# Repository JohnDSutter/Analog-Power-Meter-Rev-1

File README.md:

# Analog Power Meter Rev 1
 Analog RF Power Meter Designed as a CalQRP Club Project

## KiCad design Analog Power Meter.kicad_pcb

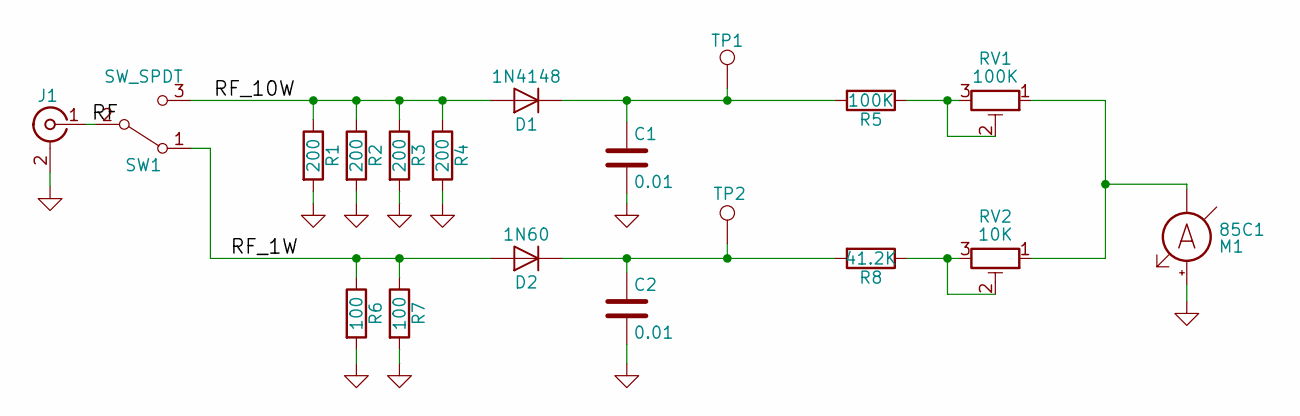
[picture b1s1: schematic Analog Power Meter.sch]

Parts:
C1, C2: 0.01; C_Disc_D3.4mm_W2.1mm_P2.50mm
D1: 1N4148; D_A-405_P7.62mm_Horizontal
D2: 1N60; D_A-405_P12.70mm_Horizontal
J1: Conn_Coaxial; BNC_Socket_TYCO-AMP_LargePads
M1: 85C1; WireConnection_1.00mmDrill
R1, R2, R3, R4: 200; R_Axial_DIN0617_L17.0mm_D6.0mm_P25.40mm_Horizontal
R5: 100K; R_Axial_DIN0207_L6.3mm_D2.5mm_P10.16mm_Horizontal
R6, R7: 100; R_Axial_DIN0207_L6.3mm_D2.5mm_P10.16mm_Horizontal
R8: 41.2K; R_Axial_DIN0207_L6.3mm_D2.5mm_P10.16mm_Horizontal
RV1: 100K; Potentiometer_Trimmer_Bourns_3296W
RV2: 10K; Potentiometer_Trimmer_Bourns_3296W
SW1: SW_SPDT; SW_CuK_OS102011MA1QN1_SPDT_Angled
TP1, TP2: TEST_1P; SolderWirePad_single_1-5mmDrill

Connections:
/RF: J1.1 (In), SW1.2 (B)
/RF_1W: D2.2 (A), R6.1, R7.1, SW1.1 (A)
/RF_10W: D1.2 (A), R1.1, R2.1, R3.1, R4.1, SW1.3 (C)
GND: C1.2, C2.2, J1.2 (Ext), M1.2 (+), R1.2, R2.2, R3.2, R4.2, R6.2, R7.2, SW1.4, SW1.5
unnamed: C1.1, D1.1 (K), R5.2, TP1.1
unnamed: C2.1, D2.1 (K), R8.2, TP2.1
unnamed: M1.1 (-), RV1.1, RV2.1
unnamed: R5.1, RV1.2, RV1.3
unnamed: R8.1, RV2.2, RV2.3

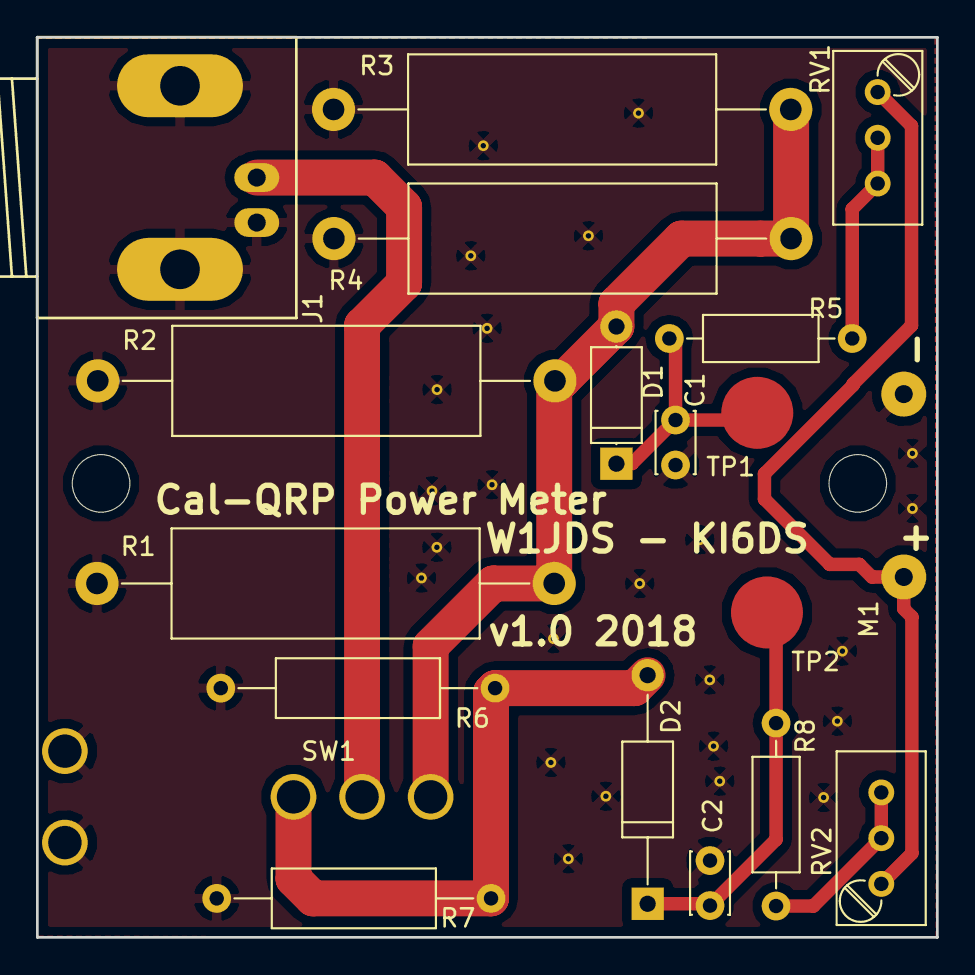
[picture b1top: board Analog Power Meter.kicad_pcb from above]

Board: 2 copper layers, 50.0 x 50.0 mm, 19 parts (0 on the bottom side), 9 nets.

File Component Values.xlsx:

Reference | Component | Value/PN | Rating
C1, C2 | Ceramic Capacitor | 0.01 | 50 V
D1 | Diode, Silicon | 1N4148
D2 | Diode, Germanium | 1N60
J1 | BNC Connector | Through-hole or panel mount
M1 | Meter | 85C1 | 200 uA
RV1 | Trim pot | 100 K
RV2 | Trim pot | 10 K
R1-R4 | Metal film Resistor | 200 | 3 W
R5 | Metal film Resistor | 100 K | 1/4 W
R6, R7 | Metal film Resistor | 100 | 1/2 W
R8 | Metal film Resistor | 41.2 K | 1/4 W
SW1 | SPDT Switch | C&K 7101MD9AV2BE or panel mount

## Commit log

2021-12-27 Adding to my projects
    Adding old work
